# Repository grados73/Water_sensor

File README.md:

# Project Name
> Water ESP Sensor

## Table of contents
* [General info](#general-info)
* [Screenshots](#screenshots)
* [Technologies](#technologies)
* [Features](#features)
* [Status](#status)
* [Inspiration](#inspiration)
* [Contact](#contact)

## General info
When I put the almost 600l aquarium in my flat, my wife was afraid of flooding the apartment. To calm her down I designed, programmed and made my own PCB with ESP8266.
The device, if it detects water on any of the two connected sensors, sends messages via a Telegram app and generate sound signal.

## Screenshots

## Technologies
C,
Arduino IDE.

## Features
-Send message via a Telegram when detect water,
-When asked, he replies informing us about the temperature, air humidity and battery voltage.

To-do list:
* Low battery level alarm.

## Status
It is working, maybe someday I will do v.1.1.

## Inspiration
Commercial devices are expensive or have limited features.

## Contact
Created by https://www.linkedin.com/in/kamil-gradowski-8706991aa - feel free to contact me!
grados73

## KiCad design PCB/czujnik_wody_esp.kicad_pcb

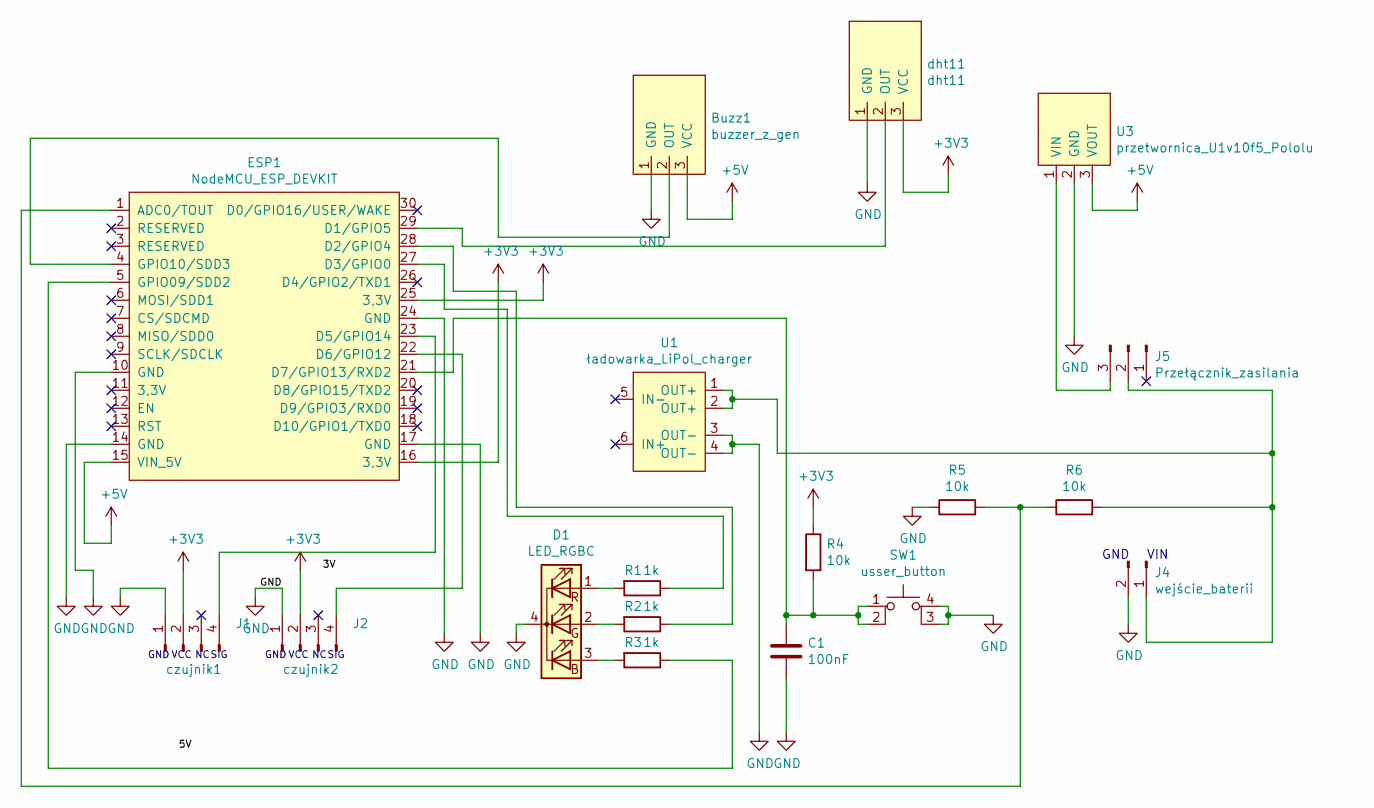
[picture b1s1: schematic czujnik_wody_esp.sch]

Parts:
Buzz1: buzzer_z_gen
C1: 100nF; CP_Radial_D4.0mm_P1.50mm
D1: LED_RGBC; LED_D5.0mm-4_RGB
ESP1: NodeMCU_ESP_DEVKIT; devkit1.0_NodeMCU_esp
J1: czujnik1; PinHeader_1x04_P2.00mm_Vertical
J2: czujnik2; PinHeader_1x04_P2.00mm_Vertical
J4: wejście_baterii; PinSocket_1x02_P2.54mm_Horizontal
J5: Przełącznik_zasilania; PinSocket_1x03_P2.54mm_Vertical
R1, R2, R3: 1k; R_Axial_DIN0207_L6.3mm_D2.5mm_P7.62mm_Horizontal
R4, R5, R6: 10k; R_Axial_DIN0207_L6.3mm_D2.5mm_P7.62mm_Horizontal
SW1: usser_button; SW_PUSH_6mm_H5mm
U1: ładowarka_LiPol_charger
U3: przetwornica_U1v10f5_Pololu; przetwornica_u1v10f5_pololu
dht11: dht11; buzzer_z_gen

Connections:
+3V3: ESP1.16 (3,3V), ESP1.25 (3,3V), J1.2, J2.2, R4.1, dht11.3 (VCC)
+5V: Buzz1.3 (VCC), ESP1.15 (VIN_5V), U3.3 (VOUT)
GND: Buzz1.1 (GND), C1.2, D1.4 (K), ESP1.10 (GND), ESP1.14 (GND), ESP1.17 (GND), ESP1.24 (GND), J1.1, J2.1, J4.2, R5.1, SW1.3 (K), SW1.4 (A), U1.3 (OUT-), U1.4 (OUT-), U3.2 (GND), dht11.1 (GND)
unnamed: Buzz1.2 (OUT), ESP1.4 (GPIO10/SDD3)
unnamed: C1.1, ESP1.21 (D7/GPIO13/RXD2), R4.2, SW1.1, SW1.2
unnamed: D1.1 (RA), R1.2
unnamed: D1.2 (GA), R2.2
unnamed: D1.3 (BA), R3.2
unnamed: ESP1.1 (ADC0/TOUT), R5.2, R6.1
unnamed: ESP1.5 (GPIO09/SDD2), R3.1
unnamed: ESP1.22 (D6/GPIO12), J2.4
unnamed: ESP1.23 (D5/GPIO14), J1.4
unnamed: ESP1.27 (D3/GPIO0), R1.1
unnamed: ESP1.28 (D2/GPIO4), R2.1
unnamed: ESP1.29 (D1/GPIO5), dht11.2 (OUT)
unnamed: J4.1, J5.2, R6.2, U1.1 (OUT+), U1.2 (OUT+)
unnamed: J5.3, U3.1 (VIN)

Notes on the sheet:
VIN
GND
GND
VCC
SIG

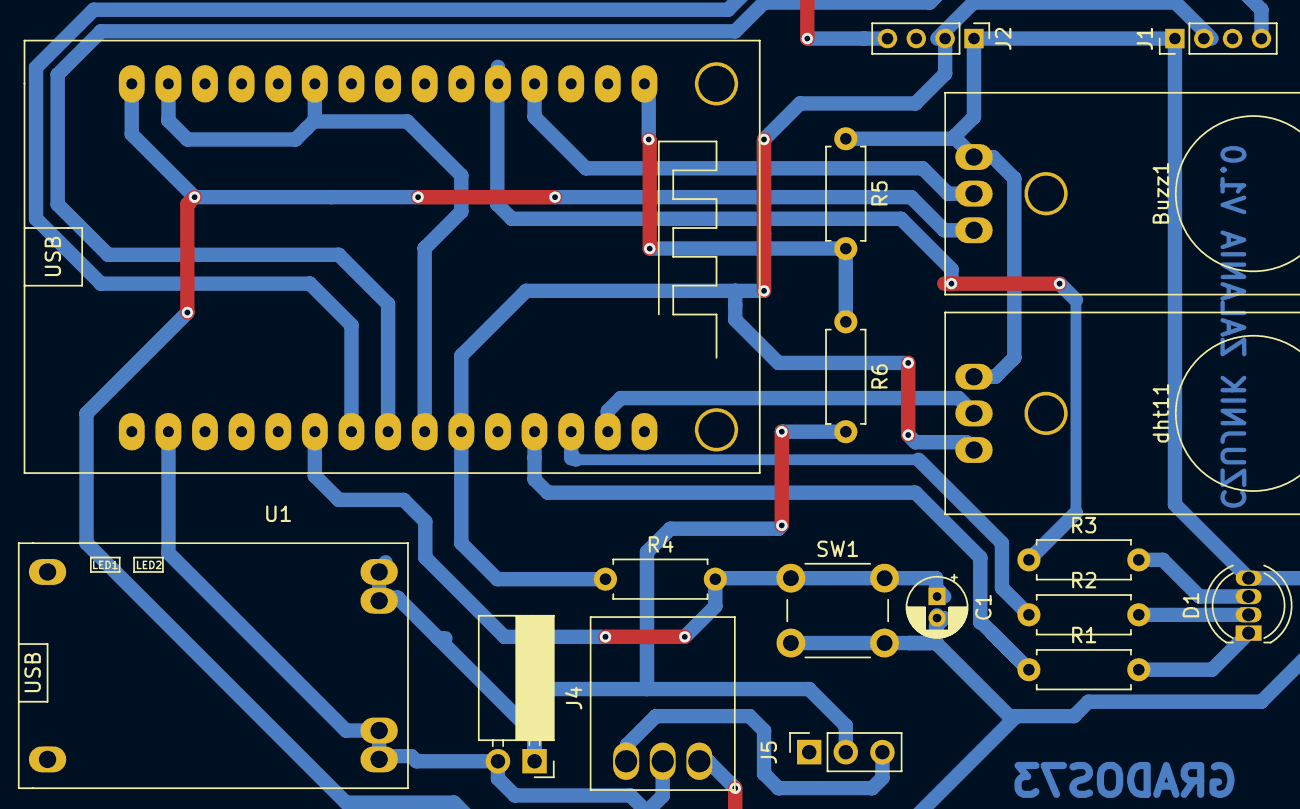
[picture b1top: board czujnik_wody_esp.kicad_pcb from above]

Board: 2 copper layers, 18 parts (0 on the bottom side), 17 nets.

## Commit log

2020-11-02 dziala telegram z 1 czujnikiem detekcji wody, przed zmiana nazwy funkcji
2020-11-02 działa z jednym czujnikiem nazwy zmiennych i funkcji już poprawne
2020-11-03 działa DHT11, ale w loop-ie i nie wysyla nic do telegramu
2020-11-03 działa DHT11, dziala telegram request o temperature i wilgotnosc
2020-11-03 dodalem komentarze opisujace dzialanie funkcji itp
2020-11-03 dziala juz funkcja wylaczajaca alarm po ustalonym czasie, na razie alarm to tylko dioda jedna
2020-11-03 dziala buzzer i dioda jako alarm
2020-11-03 pokazuje jakas wartosc jako napiecie, ale trzeba podzielic przez rozdzielczosc przetwornika
2021-02-09 Dodane zdjęcia
2021-02-09 Dodane README.md
2021-03-29 Add PCB project
2021-03-29 Add PCB img1
2021-03-29 Add KiCad PCB photo
